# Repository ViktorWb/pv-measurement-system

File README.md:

## Remote MPPT measurement and logging system for solar modules

This repository contains the code for a remote measurement system for PV modules. It also contains the KiCad files which were used to create the PCB.

### Configuration

Before compiling, edit the encryption key in `src/encryption/mod.rs`. If you don't do this you will get a compile error. Edit this once and keep it the same for all senders and receivers.

The code takes a number of configuration parameters. For the sender, these are:

- USE_DISPLAY: Set this to false to disable all communications with the screen (in case the device does not have a screen for example).
- NONCE_MIN/NONCE_MAX: A range of nonces to use for this device. Both must be between 0 and 65535. The range should be unique for each sender such that there are no overlaps, and the range should be at least 200 long. For example, for one device NONCE_MIN=1000, NONCE_MAX=1199, and for another device NONCE_MIN=1200, NONCE_MAX=1399.
- DEVICE_ID: A unique id in the range 0-127. The InfluxDB "host" field will be set to "ttgo<DEVICE_ID>", for example "ttgo25" for DEVICE_ID=25.

For the receiver, the only configuration parameter is USE_DISPLAY.

The configuration parameters are passed as environment variables to the `cargo build` command, or as build arguments to Docker.

## Compiling

In order to not have to install a bunch of stuff (ESP-IDF development framework and forked version of rust with ESP32 support), the program can be compiled in Docker.

Before continuing, make sure to install Docker engine, and that the `docker` command (or `sudo docker`) is available.

The first time you run any of the following commands it takes a long time (15 minutes), but it shouldn't take too long the next time.

### Sender

To compile the sender, run the following command in this repository:

`docker build . -t measurement-sender --build-arg FEATURES=sender --build-arg USE_DISPLAY=true --build-arg NONCE_MIN=1000 --build-arg NONCE_MAX=1199 --build-arg DEVICE_ID=75`

(Edit the values USE_DISPLAY, NONCE_MIN, NONCE_MAX and DEVICE_ID as necessary before each compile).

You now have a Docker image named `measurement-sender` on your computer. It contains the built code.

Now run one of the following:

- Linux: `docker run -v .:/dir -it measurement-sender cp /usr/src/app/target/xtensa-esp32-espidf/release/pv-measurement-system /dir/sender.elf`
- Windows : `docker run -v ${PWD}:/dir -it measurement-sender cp /usr/src/app/target/xtensa-esp32-espidf/release/pv-measurement-system /dir/sender.elf`

This will copy the built code to the file `sender.elf` in your current directory, which you can load onto the ESP32. One way of doing this is:

- Install Rust (https://rustup.rs)
- Run `cargo install espflash`
- Run `espflash --monitor ./sender.elf`.

### Receiver

To compile the sender, run the following command in this repository:

`docker build . -t measurement-receiver --build-arg FEATURES=receiver --build-arg USE_DISPLAY=true`

(Edit the value USE_DISPLAY as necessary before each compile).

You now have a Docker image named `measurement-receiver` on your computer. It contains the built code.

Now run one of the following:

- Linux: `docker run -v .:/dir -it measurement-receiver cp /usr/src/app/target/xtensa-esp32-espidf/release/pv-measurement-system /dir/receiver.elf`
- Windows : `docker run -v ${PWD}:/dir -it measurement-receiver cp /usr/src/app/target/xtensa-esp32-espidf/release/pv-measurement-system /dir/receiver.elf`

This will copy the built code to the file `receiver.elf` in your current directory, which you can load onto the ESP32. One way of doing this is:

- Install Rust (https://rustup.rs)
- Run `cargo install espflash`
- Run `espflash --monitor ./receiver.elf`.

### Without Docker

If you do not want to compile in docker, follow the instructions at `https://esp-rs.github.io/book/installation/index.html` to install the required tools. Here's a quick summary:

- Install rust (https://rustup.rs/)
- Install XTensa target: `cargo install espup && espup install`
- Install espflash: `cargo install cargo-espflash`

On windows, we also had to install ESP-IDF under "manual installation" at (https://docs.espressif.com/projects/esp-idf/en/latest/esp32/get-started/).

Also, make sure to "source" you current shell:

- Linux: `. ~/export-esp.sh`
- Windows: We had to run inside the ESP_IDF development environment.

Then, to compile and load the code onto the device simply run:

Linux:

- Sender: `USE_DISPLAY=true NONCE_MIN=1000 NONCE_MAX=1199 DEVICE_ID=75 cargo run --features sender`
- Receiver: `USE_DISPLAY=true cargo run --features receiver`

Windows:

- Sender: `$env:USE_DISPLAY = "true"; $env:NONCE_MIN = 1000; $env:NONCE_MAX = 1199; $env:DEVICE_ID = 75; cargo run --features sender`
- Receiver: `$env:USE_DISPLAY = "true" cargo run --features receiver`

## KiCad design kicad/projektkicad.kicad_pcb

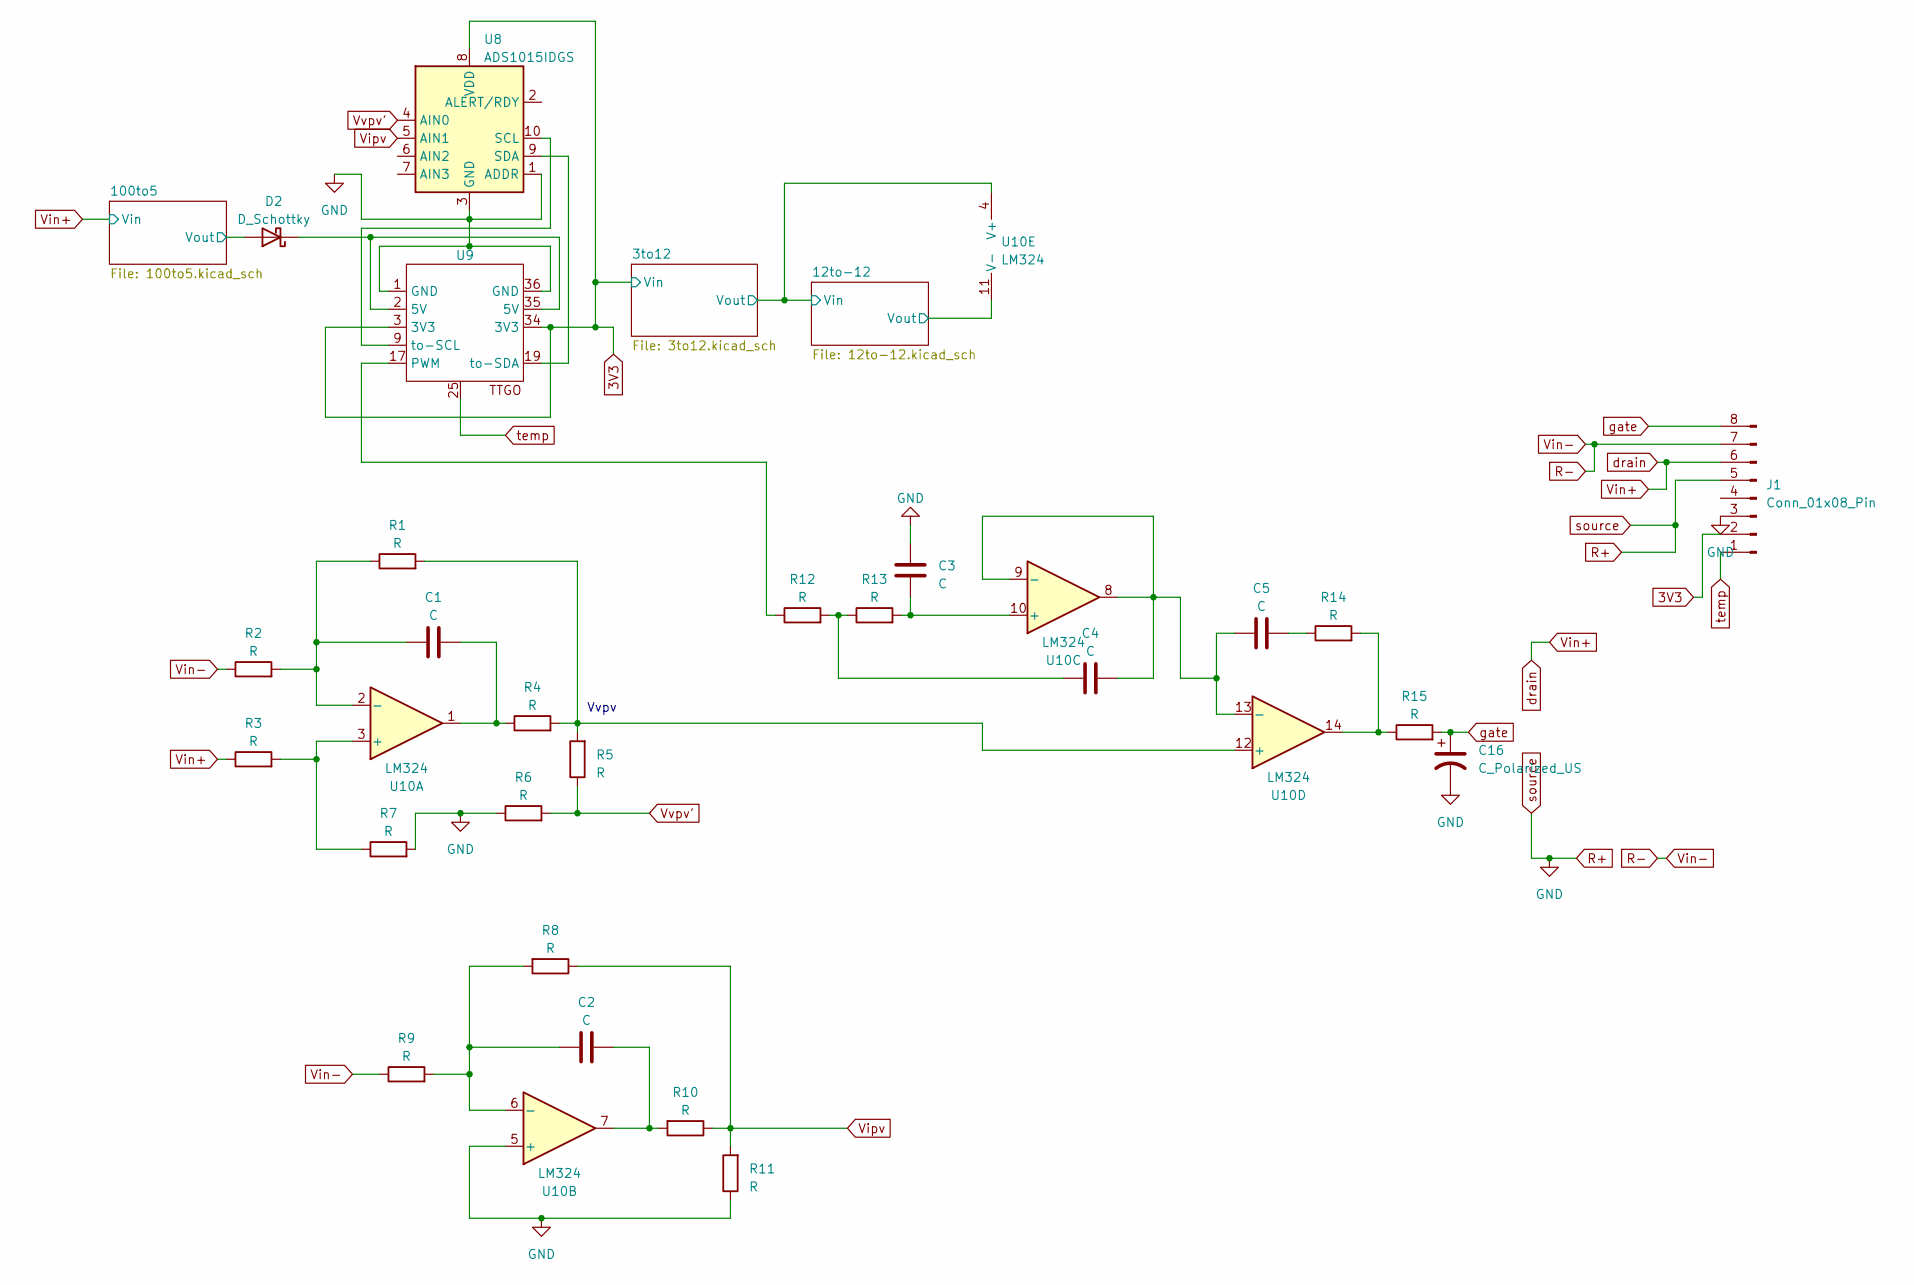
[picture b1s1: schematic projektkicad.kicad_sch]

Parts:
C1, C2, C3, C4, C5: C; C_0805_2012Metric_Pad1.18x1.45mm_HandSolder
C16: C_Polarized_US; CP_Radial_D10.0mm_P5.00mm
D2: D_Schottky; D_SMA_Handsoldering
J1: Conn_01x08_Pin; PhoenixContact_MCV_1,5_8-G-5.08_1x08_P5.08mm_Vertical
R1, R2, R3, R4, R5, R6, R7, R8, R9, R10, R11, R12, R13, R14, R15: R; R_0805_2012Metric_Pad1.20x1.40mm_HandSolder
U8: ADS1015IDGS; TSSOP-10_3x3mm_P0.5mm
U9: ttgo
U10: LM324; SOIC-14_3.9x8.7mm_P1.27mm

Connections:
3V3: J1.2, U8.8 (VDD), U9.3 (3V3), U9.34 (3V3); also elsewhere on the board
/12to-12/Vin: U10.4 (V+); also elsewhere on the board
/12to-12/Vout: U10.11 (V-); also elsewhere on the board
unnamed: C1.2, R4.1, U10.1
unnamed: C2.2, R10.2, U10.7
unnamed: C4.1, R12.2, R13.1
unnamed: C5.2, R14.1
unnamed: R14.2, R15.1, U10.14
unnamed: U8.10 (SCL), U9.9 (to-SCL)
unnamed: U8.9 (SDA), U9.19 (to-SDA)
unnamed: R12.1, U9.17 (PWM)
unnamed: R3.2, R7.1, U10.3 (+)
unnamed: C1.1, R1.1, R2.2, U10.2 (-)
unnamed: C2.1, R8.2, R9.2, U10.6 (-)
unnamed: C3.1, R13.2, U10.10 (+)
unnamed: C4.2, C5.1, U10.8, U10.9 (-), U10.13 (-)
unnamed: R1.2, R4.2, R5.2, U10.12 (+)
R+: C3.2, C16.2, D2.2 (A), J1.3, J1.5, R6.1, R7.2, R11.1, U8.1 (ADDR), U8.3 (GND), U9.1 (GND), U9.36 (GND), U10.5 (+); also elsewhere on the board
R-: J1.7, R2.1, R9.1
Vin+: J1.6, R3.1; also elsewhere on the board
Vipv: R8.1, R10.1, R11.2, U8.5 (AIN1)
Vvpv': R5.1, R6.2, U8.4 (AIN0)
temp: J1.1, U9.25

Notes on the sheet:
Vvpv

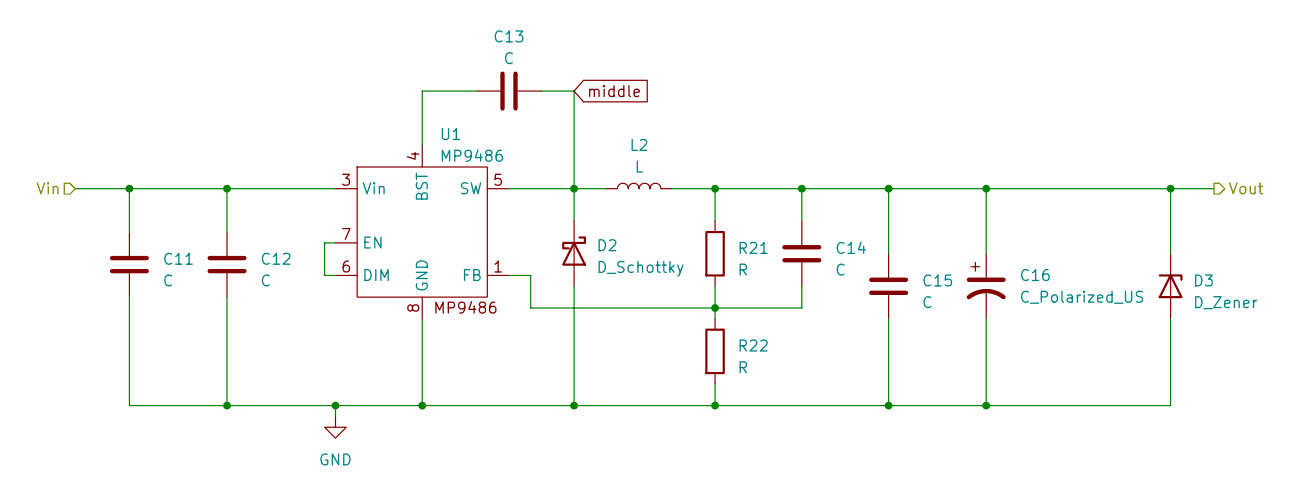
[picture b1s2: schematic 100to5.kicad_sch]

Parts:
C11, C12: C; C_1210_3225Metric_Pad1.33x2.70mm_HandSolder
C13, C14, C15: C; C_0805_2012Metric_Pad1.18x1.45mm_HandSolder
C16: C_Polarized_US; CP_Radial_D10.0mm_P5.00mm
D2: D_Schottky; D_SMA_Handsoldering
D3: D_Zener; D_SMA_Handsoldering
L2: L; L_Bourns-SRN6028
R21, R22: R; R_0805_2012Metric_Pad1.20x1.40mm_HandSolder
U1: MP9486; SOIC-8_3.9x4.9mm_P1.27mm

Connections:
unnamed: C13.2, U1.4 (BST)
unnamed: U1.6 (DIM), U1.7 (EN)
unnamed: C14.2, R21.2, R22.1, U1.1 (FB)
R+: C11.2, C12.1, C15.1, C16.2, D2.2 (A), D3.2 (A), R22.2, U1.8 (GND); also elsewhere on the board
Vin+: C11.1, C12.2, U1.3 (Vin); also elsewhere on the board

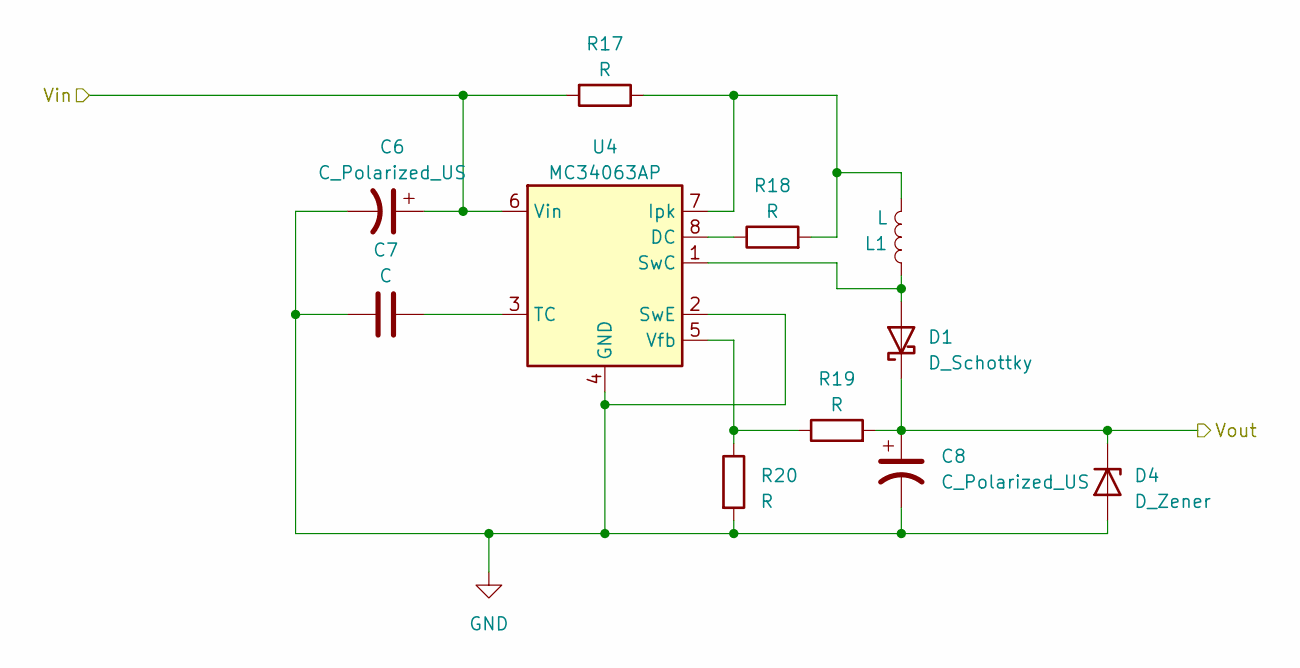
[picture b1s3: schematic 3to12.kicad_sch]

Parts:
C6, C8: C_Polarized_US; CP_Radial_D10.0mm_P5.00mm
C7: C; C_0805_2012Metric_Pad1.18x1.45mm_HandSolder
D1: D_Schottky; D_SMA_Handsoldering
D4: D_Zener; D_SMA_Handsoldering
L1: L; L_Bourns-SRN6028
R17, R18, R19, R20: R; R_0805_2012Metric_Pad1.20x1.40mm_HandSolder
U4: MC34063AP; DIP-8_W7.62mm

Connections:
3V3: C6.1, R17.2; also elsewhere on the board
/12to-12/Vin: C8.1, D1.1 (K), D4.1 (K), R19.2; also elsewhere on the board
unnamed 7: D1.2 (A), L1.1; also elsewhere on the board
unnamed 12: R18.1; also elsewhere on the board
unnamed 13: L1.2, R17.1, R18.2; also elsewhere on the board
unnamed 14: C7.2; also elsewhere on the board
unnamed 15: R19.1, R20.1; also elsewhere on the board
R+: C6.2, C7.1, C8.2, D4.2 (A), R20.2; also elsewhere on the board

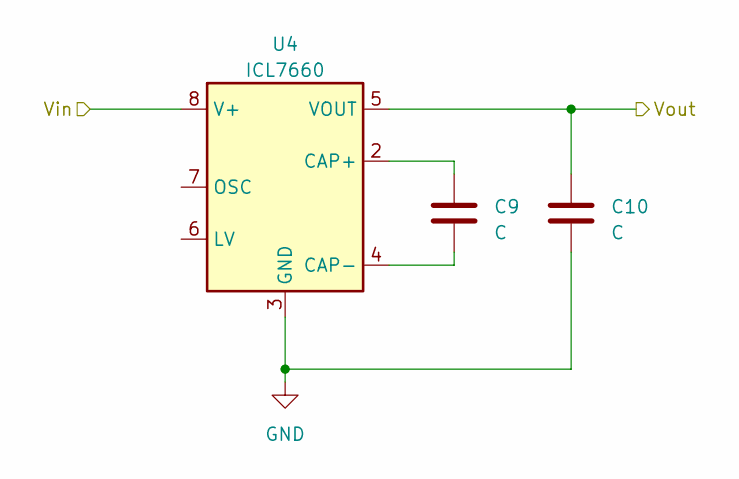
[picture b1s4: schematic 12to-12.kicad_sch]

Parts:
C9, C10: C; C_0805_2012Metric_Pad1.18x1.45mm_HandSolder
U4: ICL7660; SOIC-8_3.9x4.9mm_P1.27mm

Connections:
/12to-12/Vout: C10.1; also elsewhere on the board
unnamed 16: C9.1; also elsewhere on the board
unnamed 17: C9.2; also elsewhere on the board
R+: C10.2; also elsewhere on the board

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
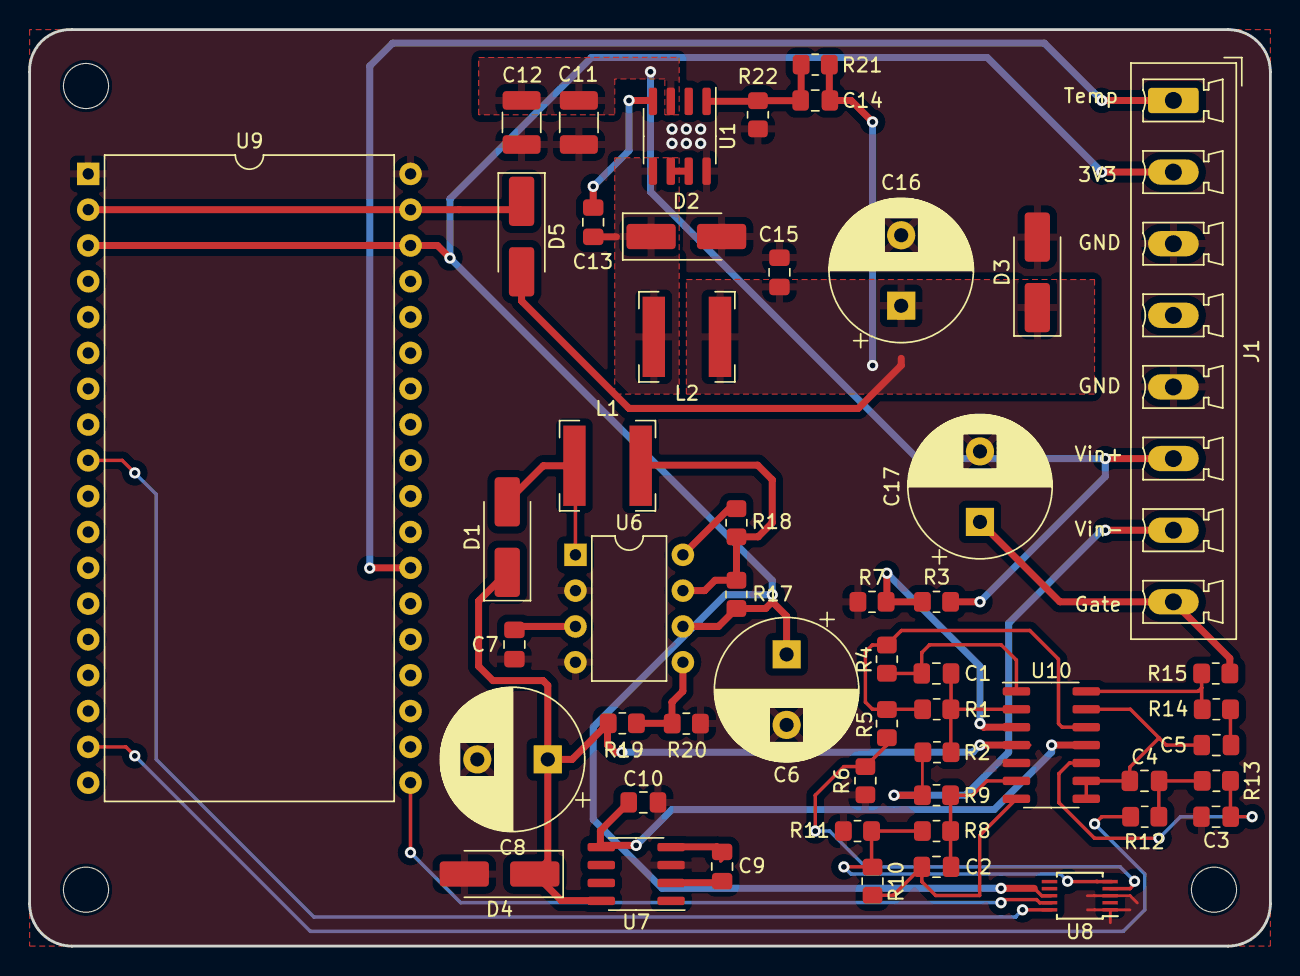
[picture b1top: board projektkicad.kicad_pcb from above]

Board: 2 copper layers, 88.0 x 65.0 mm, 52 parts (0 on the bottom side), 37 nets.

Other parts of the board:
C17: C_Polarized_US; CP_Radial_D10.0mm_P5.00mm
D5: D_Schottky; D_SMA_Handsoldering
U6: MC34063AP; DIP-8_W7.62mm
U7: ICL7660; SOIC-8_3.9x4.9mm_P1.27mm

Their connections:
3V3: U6.6 (Vin); also elsewhere on the board
/12to-12/Vin: U7.8 (V+); also elsewhere on the board
/12to-12/Vout: U7.5 (VOUT); also elsewhere on the board
unnamed 7: U6.1 (SwC); also elsewhere on the board
unnamed 12: U6.8 (DC); also elsewhere on the board
unnamed 13: U6.7 (Ipk); also elsewhere on the board
unnamed 14: U6.3 (TC); also elsewhere on the board
unnamed 15: U6.5 (Vfb); also elsewhere on the board
unnamed 16: U7.2 (CAP+); also elsewhere on the board
unnamed 17: U7.4 (CAP-); also elsewhere on the board
R+: C17.2, U6.2 (SwE), U6.4 (GND), U7.3 (GND); also elsewhere on the board

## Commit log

2023-06-06 Copy over everything
2023-06-08 Added KiCad files
